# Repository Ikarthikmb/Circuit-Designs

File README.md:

# Circuit-Designs

## Contents:
1. [Breadboard power supply](#1-breadboard-power-supply)
2. [Raspberry Pi FS Hat v01](#2-raspberry-pi-fs-hat-v01)
3. [Arduino Battery Powered clone with extended EEPROM and clock(BACEE)](#5-project-bacee)
4. [Op Amp Logarthmic amplifier](#6-op-amp-log-amplifier)

---

## [1-Breadboard Power Supply](#contents)

- Converts the input ac/dc voltage(which does not exceed 35V) to output of 5 volts. This can be used to power circuits that require 5V as input supply for example Arduino(Requires 5V input power supply).
- **Connections:** Connect a input power supply to the jack and the output is obtained fron pin heads.
- To view/modify the source file, download the repository and navigate to `1-Breadboard Power Supply` folder and open the `bread power supply schematic.pro` project file in KiCAD.

|3D View||
|---|---|
|Schematic Diagram| |

## [2-Raspberry Pi FS Hat v01](#contents)

- Connecting a DHT11/12 sensor to the raspberry pi. 
- To view/modify the source file, download the repository and navigate to `2-Raspberry Pi FS Hat v01` folder and open the `2-Raspberry Pi FS Hat v01.pro` project file in KiCAD.

|3D View||
|---|---|
|Schematic Diagram| |

## [5-Project BACEE](#contents)

|||
|---|---|
|Front view|Back view|

- This is Arduino Battery Powered clone with extended EEPROM and clock. 
- To view/modify the source file, download the repository and navigate to `5-Project BACEE` folder and open the `5-Project BACEE.pro` project file in KiCAD or click [here](https://github.com/Ikarthikmb/Circuit-Designs/tree/master/5-Project%20BACEE) to navigate to repo.

## [6-OP-Amp Log Amplifier](#contents)
|  |  |
|---|---|
| Schematic | Waveform |

A log amplifier is an amplifier for which the output voltage Vout is K times the natural log of the input voltage Vin. Logarithmic amplifiers are used to perform mathematical operations like multiplication, division and exponentiation.

---

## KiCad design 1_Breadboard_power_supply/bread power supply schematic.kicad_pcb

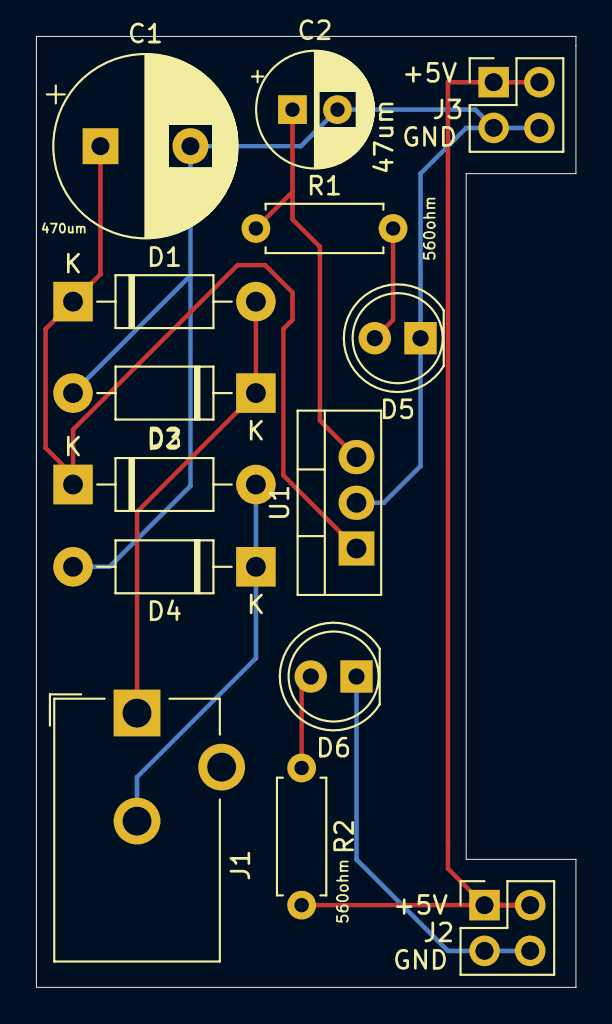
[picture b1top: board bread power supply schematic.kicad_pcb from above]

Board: 2 copper layers, 30.0 x 52.8 mm, 14 parts (0 on the bottom side), 8 nets.

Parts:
C1: CP; CP_Radial_D10.0mm_P5.00mm
C2: CP; CP_Radial_D6.3mm_P2.50mm
D1, D2, D3, D4: 1N4007; D_DO-41_SOD81_P10.16mm_Horizontal
D5, D6: LED; LED_D5.0mm
J1: Barrel_Jack_Switch; BarrelJack_CUI_PJ-102AH_Horizontal
J2, J3: Conn_02x02_Odd_Even; PinHeader_2x02_P2.54mm_Vertical
R1, R2: 560 ohm; R_Axial_DIN0207_L6.3mm_D2.5mm_P7.62mm_Horizontal
U1: LM7805_TO220; TO-220-3_Vertical

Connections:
/V-: C1.2, C2.2, D2.2, D4.2, D5.1, D6.1, J2.3, J2.4, J3.3, J3.4, U1.2
/Vin: C1.1, D1.1, D3.1, U1.1
/Vout1: C2.1, R1.1, U1.3
/Vout2: J2.1, J2.2, J3.1, J3.2, R2.2
unnamed: D1.2, D2.1, J1.1
unnamed: D3.2, D4.1, J1.2
unnamed: D5.2, R1.2
unnamed: D6.2, R2.1

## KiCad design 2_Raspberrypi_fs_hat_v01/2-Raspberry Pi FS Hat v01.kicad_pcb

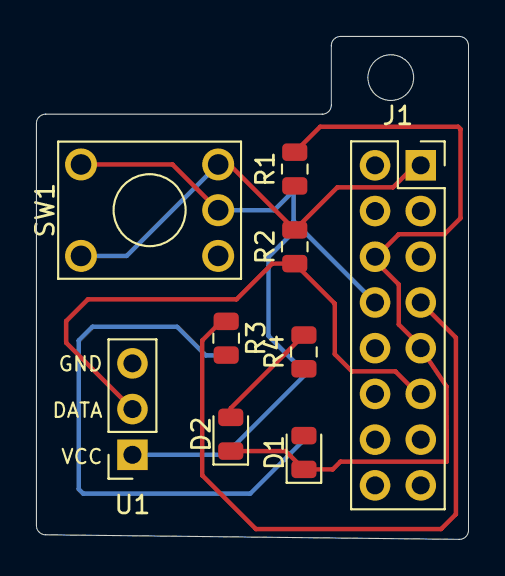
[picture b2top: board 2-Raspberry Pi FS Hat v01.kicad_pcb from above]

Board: 2 copper layers, 24.0 x 27.9 mm, 9 parts (0 on the bottom side), 7 nets.

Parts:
D1, D2: LED; LED_0805_2012Metric
J1: Raspberry_Pi_2_3; PinSocket_2x08_P2.54mm_Vertical
R1: 10k; R_0805_2012Metric
R2: 330k; R_0805_2012Metric
R3, R4: R; R_0805_2012Metric
SW1: SW_DPST; KSA_Tactile_SPST
U1: DHT22; PinSocket_1x03_P2.54mm_Vertical

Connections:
/3V3: J1.1, R2.2, R4.1, SW1.1, SW1.3, U1.1
/button_input: J1.8, R1.1, SW1.2, SW1.4
GND: D1.1, D2.1, J1.6, J1.9, R1.2
unnamed: D1.2, R3.2
unnamed: D2.2, R4.2
unnamed: J1.7, R3.1
unnamed: J1.11, R2.1, U1.2

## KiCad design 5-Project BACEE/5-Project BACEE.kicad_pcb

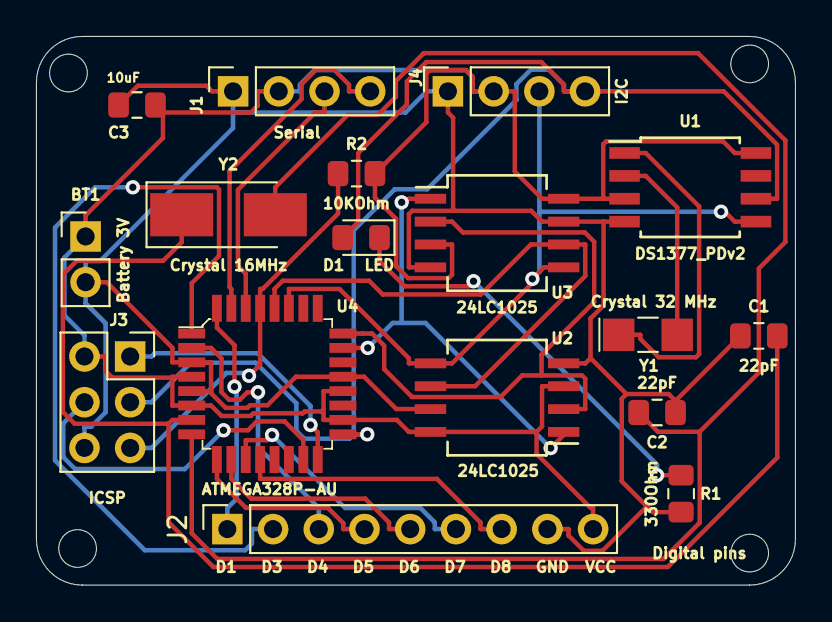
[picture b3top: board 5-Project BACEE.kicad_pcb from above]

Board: 2 copper layers, 42.2 x 30.5 mm, 17 parts (0 on the bottom side), 24 nets.

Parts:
BT1: Battery 3V; PinHeader_1x02_P2.54mm_Vertical
C1, C2: 22pF; C_0805_2012Metric_Pad1.15x1.40mm_HandSolder
C3: 10uF; C_0805_2012Metric_Pad1.15x1.40mm_HandSolder
D1: LED; LED_0805_2012Metric_Pad1.15x1.40mm_HandSolder
J1: Serial; PinSocket_1x04_P2.54mm_Vertical
J2: Digital pins; PinSocket_1x09_P2.54mm_Vertical
J3: ICSP; PinSocket_2x03_P2.54mm_Vertical
J4: I2C; PinSocket_1x04_P2.54mm_Vertical
R1: 330Ohm; R_0805_2012Metric_Pad1.15x1.40mm_HandSolder
R2: 10KOhm; R_0805_2012Metric_Pad1.15x1.40mm_HandSolder
U1: DS1377_PDv2; SOIJ-8_5.3x5.3mm_P1.27mm
U2, U3: 24LC1025; SO-8_5.3x6.2mm_P1.27mm
U4: ATMEGA328P-AU; TQFP-32_7x7mm
Y1: Crystal 32 MHz; Crystal_SMD_MicroCrystal_CC7V-T1A-2Pin_3.2x1.5mm_HandSolder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
Y2: Crystal 16MHz; Crystal_SMD_5032-2Pin_5.0x3.2mm_HandSoldering

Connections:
/ADDS1: U2.1, U3.1, U4.23
/ADDS2: U2.2, U3.2, U4.24
/D2: J2.1, U4.32
/D3: J2.2, U4.1
/D4: J2.3, U4.2
/D5: J2.4, U4.9
/D6: J2.5, U4.10
/D7: J2.6, U4.11
/D8: J2.7, U4.12
/MISO: J3.1, U4.16
/MOSI: J3.4, U4.15
/RESET: J3.5, R2.1, U4.29
/RX: J1.3, U4.30
/SCK: D1.2, J3.3, J4.4, U1.6, U4.17
/SCL: U2.6, U3.6, U4.28
/SDA: J4.3, U1.5, U2.5, U3.5, U4.27
/TX: J1.4, U4.31
/Vcc: BT1.1, C3.1, J1.2, J2.9, J3.2, J4.2, R2.2, U1.3, U1.8, U2.3, U2.8, U3.3, U3.8, U4.4, U4.6, U4.18, U4.20
GND: BT1.2, C1.1, C2.1, C3.2, J1.1, J2.8, J3.6, J4.1, R1.2, U1.4, U2.4, U2.7, U3.4, U3.7, U4.3, U4.5, U4.21
unnamed: C1.2, U4.7, Y2.1
unnamed: C2.2, U4.8, Y2.2
unnamed: D1.1, R1.1
unnamed: U1.1, Y1.1
unnamed: U1.2, Y1.2

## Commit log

2020-09-09 op amp log amp
2020-09-09 added log amp file
2021-04-08 Adding dc to dc project files
2021-04-08 update links
2021-04-08 Adding Gouriet_clapp_capacitive_oscillator schematic
2021-04-08 adding decimal counter
2021-04-08 updated schematic of decimal counter
2021-04-08 renamed Readme_decimal_counter to README
2021-04-08 added custom libraries for 4026 IC
    updaed readme
